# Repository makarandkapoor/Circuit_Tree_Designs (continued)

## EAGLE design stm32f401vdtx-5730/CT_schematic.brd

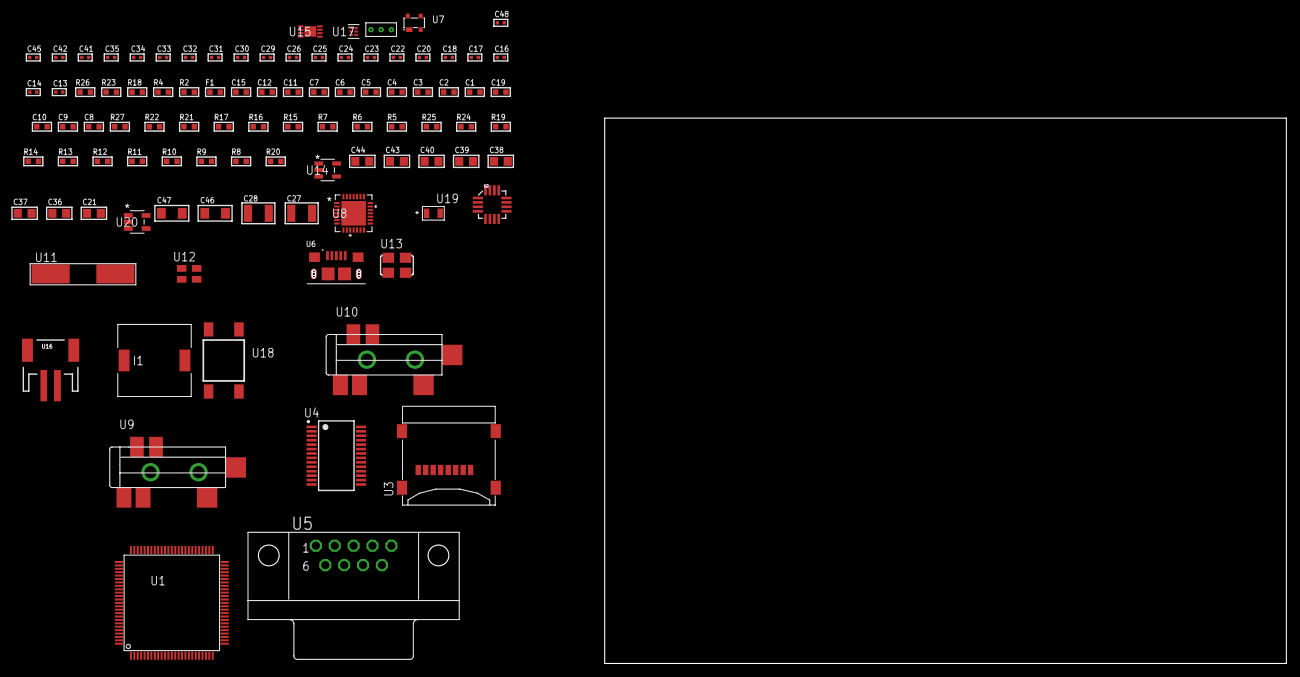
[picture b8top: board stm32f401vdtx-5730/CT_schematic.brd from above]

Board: 2 copper layers, 96 parts (0 on the bottom side), 61 nets, no tracks yet.

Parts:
C1, C12, C15: 1e-06; C0603
C2, C3, C4, C5, C6, C7: 1e-07; C0603
C8: 4.7e-06; C0603
C9, C10: 2.2e-06; C0603
C11: 1e-08; C0603
C13, C14: 1e-11; C0402
C16, C17, C18, C41, C42, C48: 1e-08; C0402
C19: 4.7e-07; C0603
C20, C22, C23, C24, C25, C26, C31, C32, C33, C34, C35, C45: 1e-07; C0402
C21, C36, C37, C38, C39, C40, C43, C44: 1e-05; C0805
C27, C28: 2.2e-05; C1210
C29, C30: 1e-09; C0402
C46, C47: 1e-05; C1206
F1: 240.0; L0603
I1: 2.5e-06; DR1040
R2: 1000.0; R0603
R4: 4700.0; R0603
R5, R6, R7, R21, R22, R27: 10000.0; R0603
R8, R9, R10, R11, R12, R13, R14: 100000.0; R0603
R15, R16, R17: 47000.0; R0603
R18: 680.0; R0603
R19: 220000.0; R0603
R20: 1000000.0; R0603
R23: 9100.0; R0603
R24: 680000.0; R0603
R25: 120000.0; R0603
R26: 2000.0; R0603
U1: STM32F401VDT6; LQFP100
U2: l3g4200d; LGA-16
U3: 0472192001; MOLEX_47219-2001
U4: ST3241EBPR; SSOP-28
U5: 182-009-113R531; 182-009-MALE
U6: 10118193-0001LF; FCI_10118193-0001LF
U7: prtr5v0u2ax; SOT143B
U8: WM8731CLSEFL; QFN-28
U9, U10: SJ-43515TS-SMT-TR
U11: ABLS-25.000MHZ-B2F-T
U12: ASEK-32.768KHz-ECST; ASEK
U13: ASFL1-12.288MHZ-EC-T; ASFL1
U14: ltc3406es5; TSOT-23-5
U15: MCP73831T-2ACI/MC; DFN8_2X3MC
U16: S2B-PH-SM4-TB(LF)(SN); JST-2-SMD
U17: TPS3895ADRYR; SON-6
U18: 4-1437565-2; SW_4-1437565-2
U19: Q65110A2395; LGM67K-G1J2-24-Z
U20: nc7sz125m5x; NC7SZ125M5X
U21: Dummy; DUMMY_PACKAGE_211

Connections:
CLK_CRYSTAL_U1_12: C13.1, U1.12, U11.1
CLK_CRYSTAL_U1_13: C14.1, U1.13, U11.2
CLK_U1_8: U1.8, U12.3
CLK_U8_1: U8.1, U13.3
GND: C1.2, C2.2, C3.2, C4.2, C5.2, C6.2, C7.2, C8.2, C9.2, C10.2, C11.2, C12.2, C13.2, C14.2, C15.2, C16.2, C17.2, C18.2, C20.2, C21.2, C22.2, C25.2, C26.2, C30.2, C31.2, C32.2, C33.2, C34.2, C35.2, C36.2, C37.2, C38.2, C39.2, C40.2, C41.2, C42.2, C43.2, C44.1, C44.2, C45.2, C46.2, C47.2, C48.2, R2.2, R5.2, R6.1, R6.2, R15.2, R16.2, R17.2, R19.2, R23.2, R25.2, R26.2, U1.10, U1.20, U1.27, U1.49, U1.70, U1.74, U1.99, U2.8, U2.9, U2.10, U2.11, U2.12, U2.13, U3.6, U3.G1, U3.G2, U3.G3, U3.G4, U4.23, U4.25, U5.5, U6.5, U6.6, U6.7, U6.8, U6.9, U7.1, U8.4, U8.15, U8.19, U8.25, U8.26, U8.29, U9.1, U10.1, U12.2, U13.2, U14.2, U15.6, U15.9, U16.2, U17.2, U19.C, U20.1, U20.3, U21.1
INPUT_USBPOWER_5V: C15.1, C46.1, R27.2, U1.68, U6.1, U7.4, U15.1, U15.2
NET_U1_14: R4.1, U1.14, U20.4
NET_U1_22: C11.1, C12.1, F1.1, U1.21, U1.22
NET_U1_48: C9.1, U1.48
NET_U1_73: C10.1, U1.73
NET_U1_94: R5.1, U1.94
NET_U1_98: U18.3, U18.4
NET_U2_14: C18.1, C19.1, U2.14
NET_U4_1: C24.1, U4.1
NET_U4_2: C24.2, U4.2
NET_U4_3: C26.1, U4.3
NET_U4_22: R14.1, U4.22
NET_U4_24: C23.2, U4.24
NET_U4_27: C25.1, U4.27
NET_U4_28: C23.1, U4.28
NET_U5_2: U4.4, U5.2
NET_U5_3: U4.9, U5.3
NET_U5_7: U4.5, U5.7
NET_U5_8: U4.10, U5.8
NET_U8_20: C35.1, C40.1, U8.20
NET_U9_2: C28.1, R16.1, U9.2
NET_U9_5: C27.1, R15.1, U9.5
NET_U10_5: C29.1, C30.1, R17.1, R18.1, U10.5
NET_U14_3: I1.1, U14.3
NET_U14_5: R19.1, R20.1, U14.5
NET_U14_ATNET_3: I1.2, R20.2
NET_U15_5: R27.1, U15.5
NET_U15_8: R26.1, U15.8
NET_U17_1: R22.1, R23.1, U17.1
NET_U17_3: R24.2, R25.1, U17.3
NET_U17_4: R21.1, U17.4, U20.2
NET_U18_1: R2.1, U18.1, U18.2
PROC_I2S2_CK: U1.47, U8.7
PROC_I2S2_EXT_SD: U1.17, U8.10
PROC_I2S2_SD: U1.18, U8.8
PROC_I2S2_WS: U1.51, U8.9, U8.11
PROC_SDIO_CK: R9.1, U1.80, U3.5
PROC_SDIO_CMD: R8.1, U1.83, U3.3
PROC_SDIO_D0: R10.1, U1.65, U3.7
PROC_SDIO_D1: R11.1, U1.66, U3.8
PROC_SDIO_D2: R12.1, U1.78, U3.1
PROC_SDIO_D3: R13.1, U1.79, U3.2
PROC_SPI1_MISO: U1.31, U2.4
PROC_SPI1_MOSI: U1.32, U2.3
PROC_SPI1_NSS: R7.1, U1.29, U2.5
PROC_SPI1_SCK: U1.30, U2.2
PROC_TIM1_CH2: U1.42, U21.2
PROC_TIM1_CH4: U1.45, U21.3
PROC_USART2_CTS: U1.23, U4.13
PROC_USART2_RTS: U1.24, U4.18
PROC_USART2_RX: U1.26, U4.19
PROC_USART2_TX: U1.25, U4.14
PROC_USB_OTG_FS_DM: U1.70, U6.2, U7.3
PROC_USB_OTG_FS_DP: U1.71, U6.3, U7.2
VCC_S1_3V7: C43.1, C47.1, U14.4, U15.3, U15.4, U16.1
VCC_TIER1_3V3: C1.1, C2.1, C3.1, C4.1, C5.1, C6.1, C7.1, C8.1, C16.1, C17.1, C20.1, C21.1, C22.1, C31.1, C32.1, C33.1, C34.1, C36.1, C37.1, C38.1, C39.1, C41.1, C42.1, C44.2, C45.1, C48.1, F1.2, I1.2, R4.2, R7.2, R8.2, R9.2, R10.2, R11.2, R12.2, R13.2, R14.2, R20.2, R21.2, R22.2, R24.1, U1.6, U1.11, U1.19, U1.28, U1.50, U1.75, U1.100, U2.1, U2.15, U2.16, U3.4, U4.26, U8.3, U8.5, U8.12, U8.18, U12.4, U13.4, U17.6, U20.5
